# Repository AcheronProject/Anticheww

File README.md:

# Acheron 65-SM-S-STM32-MX-TH-WI (Codename "Anticheww")

See [this page](https://gondolindrim.github.io/AcheronDocs/anticheww/intro.html) for the Anticheww documentation.

## Introduction

Anticheww was conceived as an experiment on how many layouts one can support in a single PCB. The current (v2.0.8) version is a universal 65% PCB, compatible with TADA68 and KBD67 (rev. 1 was tested and working, not tested with rev. 2 yet) supporting per-key lighting using single-color LEDs, RGB underglow using WS2812C RGB LEDs, rotary encoders and a multitude of layouts:

- Default ANSI bottom row, with and without the 0.5 units blocker;
- 7.0 units spaebar bottom row, with and without 0.5 units blocker;
- 225-125-275 and 275-125-225 split spacebar options;
- Split backspace;
- Split left and right shifts;
- ISO enter;
- ABNT and ABNT2 layouts.

## Compatible layouts

Click [here](http://raw.githubusercontent.com/AcheronProject/Anticheww/master/graphics/KLE/anticheww_kle.json) for a JSON file that can be used in [Keyboard Layout Editor](http://keyboard-layout-editor.com).

## Contributors

- Chewwy from the [Mechs on Deck](http://twitch.tv/https://www.twitch.tv/mechsondeck) channel, who became the inspiration to make a 65% PCB.
   
## Copyright notice

This project is released under the Acheron Open-Hardware License V1.3. For the license, please refer to the LICENCE.md file.

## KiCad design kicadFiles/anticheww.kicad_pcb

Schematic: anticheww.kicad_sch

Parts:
C1, C2: 100n; C_0805_2012Metric; Rating MLCC 0805 10V or more
C3, C4, C5, C6, C7, C8, C9, C10, C11, C12, C13, C14, C15, C16: 100n; C_0805_2012Metric_RGB; Rating MLCC 0805 10V or more
C17, C18, C19, C27: 100n; C_0402_1005Metric
C20, C28: 4.7u; C_0402_1005Metric
C21: 100n; C_0805_2012Metric
C22: 1u; C_0402_1005Metric
C23: 10n; C_0402_1005Metric
C24, C25: 1u; CP_EIA-3216-10_Kemet-I_Pad1.58x1.35mm_HandSolder
C26: 100u; C_0805_2012Metric
D1, D2, D3, D4, D5, D6, D7, D8, D9, D10, D11, D12, D13, D14, D15, D23, D24, D25, D26, D27, D28, D29, D30, D31, D32, D33, D34, D35, D36, D37, D45, D46, D47, D48, D49, D50, D51, D52, D53, D54, D55, D56, D57, D58, D59, D60, D61, D62, D63, D64, D65, D66, D67, D68, D69, D70, D71, D72, D73, D74, D75, D76, D77, D78, D79, D80, D81, D82, D83, D84, D85, D87: 1N4148W; D_SOD-123
D16, D17, D18, D19, D20, D21, D22, D38, D39, D40, D41, D42, D43, D44: WS2812C; LED_WS2812B_5.0x5.0mm_P3.2mm; Manufacturer Part Number WS2812C; LCSC Part Number C114587
D86: RB060M-60TR; D_SOD-123; Manufacturer Part Number RB060M-60TR; LCSC Part Number C114257
F1: mSMD110-16V; Fuse_1812_4532Metric; Manufacturer Part Number mSMD110-16V; LCSC Part Number C69691
FB1: CBG201209U121T; L_0805_2012Metric; Manufacturer Part Number CBG201209U121T; LCSC Part Number C41330
GR1: Warning Sign (ISO Enter + LED); warning_sign_3.6x3.2mm
GR2: Warning Sign (Backspace); warning_sign_3.6x3.2mm
GR3: Warning Sign (ANSI Enter + ISO Backslash LED); warning_sign_3.6x3.2mm
GR4: Warning Sign (Left shift); warning_sign_3.6x3.2mm
J1: TYPE-C-31-M-12; Manufacturer Part Number TYPE-C-31-M-12; LCSC Part Number C165948
J2: ARM JTAG; Conn_ARM_JTAG_SWD_6
J3: Extra pins; PinHeader_2x06_P1.00mm_Vertical
LED1, LED2, LED3, LED4, LED5, LED6, LED7, LED8, LED9, LED10, LED11, LED12, LED13, LED14, LED15, LED16, LED17, LED18, LED19, LED20, LED21, LED22, LED23, LED24, LED25, LED26, LED27, LED28, LED29, LED30, LED31, LED32, LED33, LED34, LED35, LED36, LED37, LED38, LED39, LED40, LED41, LED42, LED43, LED44, LED45, LED46, LED47, LED48, LED49, LED50, LED51, LED52, LED53, LED54, LED55, LED56, LED57, LED58, LED59, LED60, LED61, LED62, LED63, LED64, LED65, LED66, LED67, LED68, LED69, LED70, LED71, LED72, LED73, LED74, LED75, LED76, LED77, LED78, LED79, LED80: LED; LED_THT_2.54mm
Q1: AO3401A; SOT-23; Manufacturer Part Number AO3401A; LCSC Part Number C15127
Q2, Q3: DTC123JKAT146; SOT-23; Manufacturer Part Number DTC123JKAT146; LCSC Part Number C111724
R1, R2, R3, R4, R5, R6, R7, R8, R9, R10, R11, R12, R13, R14: 5R; R_0805_2012Metric_LEDs
R15, R16: 5.1k; R_0805_2012Metric
R17: 1k; R_0805_2012Metric
R18, R50: 100R; R_0805_2012Metric
R19, R20, R21, R22, R23, R24, R25, R26, R27, R28, R29, R30, R31, R32, R33, R34, R35, R36, R37, R38, R39, R40, R41, R42, R43, R44, R45, R46, R47, R48, R49, R51, R52, R53, R54, R55, R56, R57, R58, R59, R60, R61, R62, R63, R64, R65, R70, R71, R72, R73, R74, R75, R76, R77, R78, R79, R80, R81, R82, R83, R84, R85, R86, R87, R88, R89, R90, R91, R92, R93, R94, R95, R96: 420R; R_0805_2012Metric_LEDs
R66, R67: 100k; R_0805_2012Metric_LEDs
R68: 33k; R_0805_2012Metric
R69: 100k; R_0805_2012Metric
S1: K2-1187SQ-A4SW-06; Manufacturer Part Number K2-1187SQ-A4SW-06; LCSC Part Number C92584
SW1: ESC; MX100
SW2: 1; MX100
SW3: 2; MX100
SW4: 3; MX100
SW5: 4; MX100
SW6: 5; MX100
SW7: 6; MX100
SW8: 7; MX100
SW9: 8; MX100
SW10: 9; MX100
SW11: 0; MX100
SW12: MINUS; MX100
SW13: PLUS; MX100
SW14: LBKSP; MX100
SW15: RBKSP; MX100
SW16: 2U_BKSP; MX200
SW17: TAB; MX150
SW18: Q; MX100
SW19: W; MX100
SW20: E; MX100
SW21: R; MX100
SW22: T; MX100
SW23: Y; MX100
SW24: U; MX100
SW25: I; MX100
SW26: O; MX100
SW27: P; MX100
SW28: LBRKT; MX100
SW29: RBRKT; MX100
SW30: BKSLSH; MX150
SW31: PGUP; MX100
SW32: ISO_ENTER; MX_ISOEnter_Vertical_LED
SW33: CAPS; MX175
SW34: A; MX100
SW35: S; MX100
SW36: D; MX100
SW37: F; MX100
SW38: G; MX100
SW39: H; MX100
SW40: J; MX100
SW41: K; MX100
SW42: L; MX100
SW43: COLON; MX100
SW44: QUOTE; MX100
SW45: ENTER; MX225R
SW46: HOME; MX100
SW47: PGDN; MX100
SW48: STEPPED_CAPS; MX125
SW49: ISO_TILDE; MX100
SW50: LSHFT; MX225
SW51: ISO_BKLSH; MX100
SW52: Z; MX100
SW53: X; MX100
SW54: C; MX100
SW55: V; MX100
SW56: B; MX100
SW57: N; MX100
SW58: M; MX100
SW59: COMMA; MX100
SW60: DOT; MX100
SW61: SLSH; MX100
SW62: 175_RSHFT; MX175
SW63: UP; MX100
SW64: END; MX100
SW65: ISO_LSHFT; MX125
SW66: LCTRL_125; MX125
SW67: LGUI_125; MX125
SW68: LALT_125; MX125
SW69: SPC_625; MX625R
SW70: LEFT; MX100
SW71: DOWN; MX100
SW72: RIGHT; MX100
SW73: RALT_125; MX125
SW74: RGUI_125; MX125
SW75, SW80: 275_SPC; MX275R
SW76, SW79: SPC_125; MX125
SW77, SW78: 225_SPC; MX225R
U1: TXS0101; SOT-23-6; Manufacturer Part Number TXS0101DBVR; LCSC Part Number C132604
U2: TPD4E05U06DQAR; USON-10_2.5x1.0mm_P0.5mm; Manufacturer Part Number TPD4E05U06DQAR; LCSC Part Number C138714
U3: STM32F072CBT6; LQFP-48_7x7mm_P0.5mm; Manufacturer Part Number STM32F072CBT6; LCSC Part Number C81720
U4: MCP1700T-3302E/TT; SOT-23; Manufacturer Part Number MCP1700T-3302E/TT; LCSC Part Number C39051

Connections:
3V3: C1.2, C17.1, C18.1, C19.2, C20.2, C22.1, C23.1, C25.1, C27.2, C28.2, D86.2 (A), J2.1, J3.1, R67.1, S1.1 (A), U1.1 (VCCA), U1.5 (OE), U3.1 (VBAT), U3.9 (VDDA), U3.24 (VDD), U3.36 (VDDIO2), U3.48 (VDD), U4.2 (VO)
5V: C2.1, C24.1, D86.1 (K), F1.2, Q1.2 (S), R1.2, R2.2, R3.2, R4.2, R5.2, R6.2, R7.2, R8.2, R9.2, R10.2, R11.2, R12.2, R13.2, R14.2, R17.1, R66.1, U1.6 (VCCB), U4.3 (VI)
BOOT0: C26.2, R68.2, R69.2, U3.44 (BOOT0)
C0: SW1.1 (Col), SW17.1 (Col), SW33.1 (Col), SW48.1 (Col), SW50.1 (Col), SW65.1 (Col), SW66.1 (Col)
C1: SW2.1 (Col), SW18.1 (Col), SW34.1 (Col), SW51.1 (Col), SW67.1 (Col), U3.11 (PA1/ADC_IN1)
C2: SW3.1 (Col), SW19.1 (Col), SW35.1 (Col), SW52.1 (Col), SW68.1 (Col), U3.10 (PA0/ADC_IN0)
C3: SW4.1 (Col), SW20.1 (Col), SW36.1 (Col), SW53.1 (Col), U3.6 (PF1/OSC_OUT)
C4: SW5.1 (Col), SW21.1 (Col), SW37.1 (Col), SW54.1 (Col), SW75.1 (Col), SW78.1 (Col), U3.5 (PF0/OSC_IN)
C5: SW6.1 (Col), SW22.1 (Col), SW38.1 (Col), SW55.1 (Col), U3.4 (PC15/OSC32_OUT)
C6: SW7.1 (Col), SW23.1 (Col), SW39.1 (Col), SW56.1 (Col), SW69.1 (Col), SW76.1 (Col), SW79.1 (Col), U3.3 (PC14/OSC32_IN)
C7: SW8.1 (Col), SW24.1 (Col), SW40.1 (Col), SW57.1 (Col), U3.2 (PC13)
C8: SW9.1 (Col), SW25.1 (Col), SW41.1 (Col), SW58.1 (Col), SW77.1 (Col), SW80.1 (Col), U3.46 (SPI2_NSS/I2S2_WS/I2C1_SDA/TIM17_CH1/PB9)
C9: SW10.1 (Col), SW26.1 (Col), SW42.1 (Col), SW59.1 (Col), SW73.1 (Col), U3.45 (I2C1_SCL/TIM16_CH1/PB8)
C10: SW11.1 (Col), SW27.1 (Col), SW43.1 (Col), SW60.1 (Col), SW74.1 (Col), U3.43 (2C1_SDA/PB7)
C11: SW12.1 (Col), SW28.1 (Col), SW44.1 (Col), SW61.1 (Col), U3.42 (I2C1_SCL/PB6)
C12: SW13.1 (Col), SW29.1 (Col), SW45.1 (Col), SW49.1 (Col), SW62.1 (Col), SW70.1 (Col), U3.41 (SPI1_MOSI/I2S1_SD/TIM3_CH2/PB5)
C13: SW14.1 (Col), SW30.1 (Col), SW32.1 (Col), SW46.1 (Col), SW63.1 (Col), SW71.1 (Col), U3.40 (SPI1_MISO/I2S1_MCK/TIM3_CH1/PB4)
C14: SW15.1 (Col), SW16.1 (Col), SW31.1 (Col), SW47.1 (Col), SW64.1 (Col), SW72.1 (Col), U3.39 (SPI1_SCK/I2S1_CK/TIM2_CH2/PB3)
D+: J1.A6 (D+), J1.B6 (D+), U2.1 (IO1), U2.4 (D2+), U2.7 (NC), U2.10 (NC), U3.33 (USB_DP/PA12)
D-: J1.A7 (D-), J1.B7 (D-), U2.2 (IO2), U2.5 (D2-), U2.6 (NC), U2.9 (NC), U3.32 (USB_DM/TIM1_CH4/PA11)
EXTRA3: J3.3, U3.22 (PB11/TIM2_CH4/I2C2_SDA)
EXTRA4: J3.4, U3.25 (PB12)
EXTRA5: J3.5, U3.21 (PB10/SPI2_SCK/I2C2_SCL/TIM2_CH3)
EXTRA6: J3.6, U3.15 (PA5/ADC_IN5/DAC_OUT2)
EXTRA7: J3.7, U3.20 (PB2)
EXTRA8: J3.8, U3.14 (PA4/TIM14_CH1/ADC_IN4)
EXTRA9: J3.9, U3.19 (PB1/TIM3_CH4/TIM14_CH1/ADC_IN9)
EXTRA10: J3.10, U3.13 (PA3/TIM15_CH2/ADC_IN3)
EXTRA11: J3.11, U3.18 (PB0/TIM3_CH3/ADC_IN8)
EXTRA12: J3.12, U3.17 (PA7/TIM3_CH2/TIM14_CH1/ADC_IN7)
GND: C1.1, C2.2, C3.1, C4.1, C5.1, C6.1, C7.1, C8.1, C9.1, C10.1, C11.1, C12.1, C13.1, C14.1, C15.1, C16.1, C17.2, C18.2, C19.1, C20.1, C21.2, C22.2, C23.2, C24.2, C25.2, C26.1, C27.1, C28.1, D16.3 (VSS), D17.3 (VSS), D18.3 (VSS), D19.3 (VSS), D20.3 (VSS), D21.3 (VSS), D22.3 (VSS), D38.3 (VSS), D39.3 (VSS), D40.3 (VSS), D41.3 (VSS), D42.3 (VSS), D43.3 (VSS), D44.3 (VSS), FB1.1, J1.A1 (GND), J1.B1 (GND), J2.5, J3.2, LED1.K, LED2.K, LED3.K, LED4.K, LED5.K, LED6.K, LED7.K, LED8.K, LED9.K, LED10.K, LED11.K, LED12.K, LED13.K, LED14.K, LED15.K, LED16.K, LED17.K, LED18.K, LED19.K, LED20.K, LED21.K, LED22.K, LED23.K, LED24.K, LED25.K, LED26.K, LED27.K, LED28.K, LED29.K, LED30.K, LED31.K, LED32.K, LED33.K, LED34.K, LED35.K, LED36.K, LED37.K, LED38.K, LED39.K, LED40.K, LED41.K, LED42.K, LED43.K, LED44.K, LED45.K, LED46.K, LED47.K, LED48.K, LED49.K, LED50.K, LED51.K, LED52.K, LED53.K, LED54.K, LED55.K, LED56.K, LED57.K, LED58.K, LED59.K, LED60.K, LED61.K, LED62.K, LED63.K, LED64.K, LED65.K, LED66.K, LED67.K, LED68.K, LED69.K, LED70.K, LED71.K, LED72.K, LED73.K, LED74.K, LED75.K, LED76.K, LED77.K, LED78.K, LED79.K, LED80.K, Q2.2 (E), Q3.2 (E), R15.2, R16.2, R66.2, R67.2, R69.1, U1.2 (GND), U2.3 (GND), U2.8 (GND), U3.8 (VSSA), U3.23 (VSS), U3.35 (VSS), U3.47 (VSS), U4.1 (GND)
LED_PWM: Q2.1 (B), U3.16 (PA6/ADC_IN6/TIM3_CH1/TIM16_CH1)
NRST: C21.1, J2.3, R50.2, U3.7 (NRST)
unnamed: C3.2, D16.1 (VDD), R1.1
unnamed: C4.2, D17.1 (VDD), R2.1
unnamed: C5.2, D18.1 (VDD), R3.1
unnamed: C6.2, D19.1 (VDD), R4.1
unnamed: C7.2, D20.1 (VDD), R5.1
unnamed: C8.2, D21.1 (VDD), R6.1
unnamed: C9.2, D22.1 (VDD), R7.1
unnamed: C10.2, D38.1 (VDD), R8.1
unnamed: C11.2, D39.1 (VDD), R9.1
unnamed: C12.2, D40.1 (VDD), R10.1
unnamed: C13.2, D41.1 (VDD), R11.1
unnamed: C14.2, D42.1 (VDD), R12.1
unnamed: C15.2, D43.1 (VDD), R13.1
unnamed: C16.2, D44.1 (VDD), R14.1
unnamed: D1.2 (A), SW1.2 (Row)
unnamed: D2.2 (A), SW2.2 (Row)
unnamed: D3.2 (A), SW3.2 (Row)
unnamed: D4.2 (A), SW4.2 (Row)
unnamed: D5.2 (A), SW5.2 (Row)
unnamed: D6.2 (A), SW6.2 (Row)
unnamed: D7.2 (A), SW7.2 (Row)
unnamed: D8.2 (A), SW8.2 (Row)
unnamed: D9.2 (A), SW9.2 (Row)
unnamed: D10.2 (A), SW10.2 (Row)
unnamed: D11.2 (A), SW11.2 (Row)
unnamed: D12.2 (A), SW12.2 (Row)
unnamed: D13.2 (A), SW13.2 (Row)
unnamed: D14.2 (A), SW14.2 (Row)
unnamed: D15.2 (A), SW15.2 (Row), SW16.2 (Row)
unnamed: D16.2 (DOUT), D17.4 (DIN)
unnamed: D17.2 (DOUT), D18.4 (DIN)
unnamed: D18.2 (DOUT), D19.4 (DIN)
unnamed: D19.2 (DOUT), D20.4 (DIN)
unnamed: D20.2 (DOUT), D21.4 (DIN)
unnamed: D21.2 (DOUT), D22.4 (DIN)
unnamed: D22.2 (DOUT), D44.4 (DIN)
unnamed: D23.2 (A), SW17.2 (Row)
unnamed: D24.2 (A), SW18.2 (Row)
unnamed: D25.2 (A), SW19.2 (Row)
unnamed: D26.2 (A), SW20.2 (Row)
unnamed: D27.2 (A), SW21.2 (Row)
unnamed: D28.2 (A), SW22.2 (Row)
unnamed: D29.2 (A), SW23.2 (Row)
unnamed: D30.2 (A), SW24.2 (Row)
unnamed: D31.2 (A), SW25.2 (Row)
unnamed: D32.2 (A), SW26.2 (Row)
unnamed: D33.2 (A), SW27.2 (Row)
unnamed: D34.2 (A), SW28.2 (Row)
unnamed: D35.2 (A), SW29.2 (Row)
unnamed: D36.2 (A), SW30.2 (Row), SW32.2 (Row)
unnamed: D38.4 (DIN), D39.2 (DOUT)
unnamed: D39.4 (DIN), D40.2 (DOUT)
unnamed: D40.4 (DIN), D41.2 (DOUT)
unnamed: D41.4 (DIN), D42.2 (DOUT)
unnamed: D42.4 (DIN), D43.2 (DOUT)
unnamed: D43.4 (DIN), D44.2 (DOUT)
unnamed: D45.2 (A), SW33.2 (Row), SW48.2 (Row)
unnamed: D46.2 (A), SW34.2 (Row)
unnamed: D47.2 (A), SW35.2 (Row)
unnamed: D48.2 (A), SW36.2 (Row)
unnamed: D49.2 (A), SW37.2 (Row)
unnamed: D50.2 (A), SW38.2 (Row)
unnamed: D51.2 (A), SW39.2 (Row)
unnamed: D52.2 (A), SW40.2 (Row)
unnamed: D53.2 (A), SW41.2 (Row)
unnamed: D54.2 (A), SW42.2 (Row)
unnamed: D55.2 (A), SW43.2 (Row)
unnamed: D56.2 (A), SW44.2 (Row)
unnamed: D57.2 (A), SW45.2 (Row), SW49.2 (Row)
unnamed: D60.2 (A), SW50.2 (Row), SW65.2 (Row)
unnamed: D61.2 (A), SW51.2 (Row)
unnamed: D62.2 (A), SW52.2 (Row)
unnamed: D63.2 (A), SW53.2 (Row)
unnamed: D64.2 (A), SW54.2 (Row)
unnamed: D65.2 (A), SW55.2 (Row)
unnamed: D66.2 (A), SW56.2 (Row)
unnamed: D67.2 (A), SW57.2 (Row)
unnamed: D68.2 (A), SW58.2 (Row)
unnamed: D69.2 (A), SW59.2 (Row)
unnamed: D70.2 (A), SW60.2 (Row)
unnamed: D71.2 (A), SW61.2 (Row)
unnamed: D72.2 (A), SW62.2 (Row)
unnamed: D73.2 (A), SW63.2 (Row)
unnamed: D79.2 (A), SW73.2 (Row)
unnamed: D80.2 (A), SW74.2 (Row)
unnamed: D81.2 (A), SW70.2 (Row)
unnamed: D82.2 (A), SW71.2 (Row)
unnamed: D83.2 (A), SW72.2 (Row)
unnamed: D87.1 (K), R68.1
unnamed: D87.2 (A), Q3.1 (B), S1.2 (B)
unnamed: FB1.2, J1.S (SHIELD)
unnamed: J1.A5 (CC1), R15.1
unnamed: J1.B5 (CC2), R16.1
unnamed: LED1.A, R19.1
unnamed: LED2.A, R20.1
unnamed: LED3.A, R21.1
unnamed: LED4.A, R22.1
unnamed: LED5.A, R23.1
unnamed: LED6.A, R24.1
unnamed: LED7.A, R25.1
unnamed: LED8.A, R26.1
unnamed: LED9.A, R27.1
unnamed: LED10.A, R28.1
unnamed: LED11.A, R29.1
unnamed: LED12.A, R30.1
unnamed: LED13.A, R31.1
unnamed: LED14.A, R32.1
unnamed: LED15.A, LED16.A, R33.1
unnamed: LED17.A, R34.1
unnamed: LED18.A, R35.1
unnamed: LED19.A, R36.1
unnamed: LED20.A, R37.1
unnamed: LED21.A, R38.1
unnamed: LED22.A, R39.1
unnamed: LED23.A, R40.1
unnamed: LED24.A, R41.1
unnamed: LED25.A, R42.1
unnamed: LED26.A, R43.1
unnamed: LED27.A, R44.1
unnamed: LED28.A, R45.1
unnamed: LED29.A, R46.1
unnamed: LED30.A, R47.1
unnamed: LED31.A, R48.1
unnamed: LED32.A, R49.1
unnamed: LED33.A, LED34.A, R51.1
unnamed: LED35.A, R52.1
unnamed: LED36.A, R53.1
unnamed: LED37.A, R54.1
unnamed: LED38.A, R55.1
unnamed: LED39.A, R56.1
unnamed: LED40.A, R57.1
unnamed: LED41.A, R58.1
unnamed: LED42.A, R59.1
unnamed: LED43.A, R60.1
unnamed: LED44.A, R61.1
unnamed: LED45.A, R62.1
unnamed: LED46.A, R63.1
unnamed: LED47.A, R64.1
unnamed: LED48.A, R65.1
unnamed: LED49.A, LED50.A, R70.1
unnamed: LED51.A, R71.1
unnamed: LED52.A, R72.1
unnamed: LED53.A, R73.1
unnamed: LED54.A, R74.1
unnamed: LED55.A, R75.1
unnamed: LED56.A, R76.1
unnamed: LED57.A, R77.1
unnamed: LED58.A, R78.1
unnamed: LED59.A, R79.1
unnamed: LED60.A, R80.1
unnamed: LED61.A, R81.1
unnamed: LED62.A, R82.1
unnamed: LED63.A, R83.1
unnamed: LED64.A, R84.1
unnamed: LED65.A, R85.1
unnamed: LED66.A, R86.1
unnamed: LED67.A, R87.1
unnamed: LED68.A, LED69.A, R88.1
unnamed: LED70.A, LED71.A, LED72.A, R89.1
unnamed: LED73.A, LED74.A, R90.1
unnamed: LED75.A, R91.1
unnamed: LED76.A, R92.1
unnamed: LED77.A, R93.1
unnamed: LED78.A, R94.1
unnamed: LED79.A, R95.1
unnamed: LED80.A, R96.1
unnamed: Q1.1 (G), R18.1
unnamed: Q1.3 (D), R19.2, R20.2, R21.2, R22.2, R23.2, R24.2, R25.2, R26.2, R27.2, R28.2, R29.2, R30.2, R31.2, R32.2, R33.2, R34.2, R35.2, R36.2, R37.2, R38.2, R39.2, R40.2, R41.2, R42.2, R43.2, R44.2, R45.2, R46.2, R47.2, R48.2, R49.2, R51.2, R52.2, R53.2, R54.2, R55.2, R56.2, R57.2, R58.2, R59.2, R60.2, R61.2, R62.2, R63.2, R64.2, R65.2, R70.2, R71.2, R72.2, R73.2, R74.2, R75.2, R76.2, R77.2, R78.2, R79.2, R80.2, R81.2, R82.2, R83.2, R84.2, R85.2, R86.2, R87.2, R88.2, R89.2, R90.2, R91.2, R92.2, R93.2, R94.2, R95.2, R96.2
unnamed: Q2.3 (C), R17.2, R18.2
unnamed: Q3.3 (C), R50.1
R0: D1.1 (K), D2.1 (K), D3.1 (K), D4.1 (K), D5.1 (K), D6.1 (K), D7.1 (K), D8.1 (K), D9.1 (K), D10.1 (K), D11.1 (K), D12.1 (K), D13.1 (K), D14.1 (K), D15.1 (K), U3.30 (TIM1_CH2/PA9)
R1: D23.1 (K), D24.1 (K), D25.1 (K), D26.1 (K), D27.1 (K), D28.1 (K), D29.1 (K), D30.1 (K), D31.1 (K), D32.1 (K), D33.1 (K), D34.1 (K), D35.1 (K), D36.1 (K), D37.1 (K), U3.38 (PA15)
R1_S2: D37.2 (A), SW31.2 (Row)
R2: D45.1 (K), U3.31 (TIM1_CH3/PA10)
R2_S2: D59.2 (A), SW47.2 (Row)
R3: D60.1 (K), D61.1 (K), D62.1 (K), D63.1 (K), D64.1 (K), D65.1 (K), D66.1 (K), D67.1 (K), D68.1 (K), D69.1 (K), D70.1 (K), D71.1 (K), D72.1 (K), D73.1 (K), D74.1 (K), U3.27 (SPI2_MISO/I2S2_MCK/I2C2_SDA/TIM15_CH1/P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)
R3_S2: D58.2 (A), SW46.2 (Row)
R4: D75.1 (K), D76.1 (K), D77.1 (K), D78.1 (K), D79.1 (K), D80.1 (K), D81.1 (K), D82.1 (K), D83.1 (K), D84.1 (K), D85.1 (K), U3.29 (TIM1_CH1/PA8)
R4_S2: D74.2 (A), SW64.2 (Row)
R5: D46.1 (K), D47.1 (K), D48.1 (K), D49.1 (K), D50.1 (K), D51.1 (K), D52.1 (K), D53.1 (K), D54.1 (K), D55.1 (K), D56.1 (K), D57.1 (K), D58.1 (K), D59.1 (K), U3.12 (PA2/ADC_IN2)
RGB_3V3: U1.3 (A), U3.28 (SPI2_MOSI/I2S2_SD/PB15)
RGB_5V: D16.4 (DIN), U1.4 (B)
S1: D75.2 (A), SW66.2 (Row)
S2: D76.2 (A), SW67.2 (Row)
S3: D77.2 (A), SW68.2 (Row)
S4: D84.2 (A), SW75.2 (Row), SW78.2 (Row)
S5: D78.2 (A), SW69.2 (Row), SW76.2 (Row), SW79.2 (Row)
S6: D85.2 (A), SW77.2 (Row), SW80.2 (Row)
SWCLK: J2.4, U3.37 (SWCLK/PA14)
SWDIO: J2.2, U3.34 (SWDIO/PA13)
VBUS: F1.1, J1.A4 (VBUS), J1.B4 (VBUS)

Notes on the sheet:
6.25U (D)
275-125-225 (S2)
225-125-275 (S1)
625 (SD)
LED
6.25 blocker (DB)
SWITCH MATRIX
3V3
RGB BACKLIGHT
USB
HARD RESET
GRAPHICS
MCU

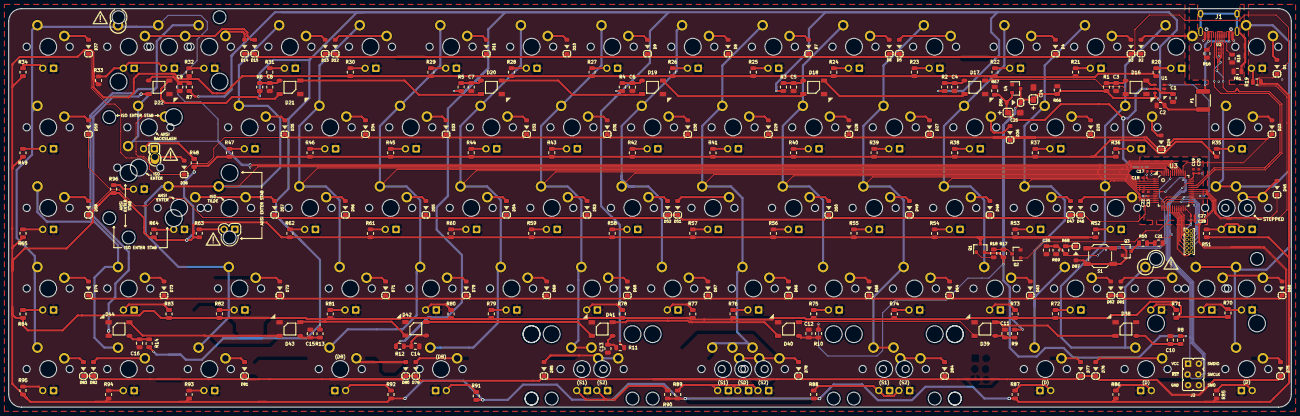
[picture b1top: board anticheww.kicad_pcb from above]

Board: 2 copper layers, 303.2 x 94.2 mm, 388 parts (0 on the bottom side), 224 nets.

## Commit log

2020-01-09 Updated RGB positions and pages petadata
2020-01-09 Add graphics folder
2020-01-18 Update AcheronLibrary
2020-07-03 Acheron Library update
2020-07-03 Placed switches, connector, mounting holes
2020-07-03 Removed measurements
2020-07-03 Route USB data lines
2020-07-16 Add RGB
2020-07-16 Added RGB level translator
2020-07-16 Add level shifter circuit to PCB
2020-07-22 Added split space and 2.75 split RShift support
2020-07-29 Route most components
2020-07-30 Add LDO circuit, route differential pair
2020-08-01 Finish routing, DRC pending
2020-08-01 Organize schematic and reset annotations
2020-08-01 Add 0.5 blocker layout options
2020-08-01 Added ANTICHEWW plated logo
2020-08-02 Fixed bottom row silkscreen markings and added ISO/ANSI enter markings
2020-08-02 Add labels, organized F.Fab
2020-08-02 Add missing maufacturer and part number to components
2020-08-02 Updated compatible layouts picture
2020-08-02 Update license to show compatible layouts
2020-08-02 Added missing fields for fuse F1. Preparing for release 2.0.8
2020-09-11 Add requried changes
    - Remove encoders support
    - Remove 7U and non-blocker bottom row options
    - Remove 2.75 right shift option
    - Remove mounting holes
    - Previous MCU pins used for encoders are now exposed as EXTRA11 and 12
2020-09-17 Changed PCB file to include plate cutouts
